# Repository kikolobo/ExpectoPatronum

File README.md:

# ExpectoPatronum_HW
Remote Lightning LED Fixture for performing lightshows. Based on NEO PIXELS, NRF24 Radios, Attiny84 MCU.

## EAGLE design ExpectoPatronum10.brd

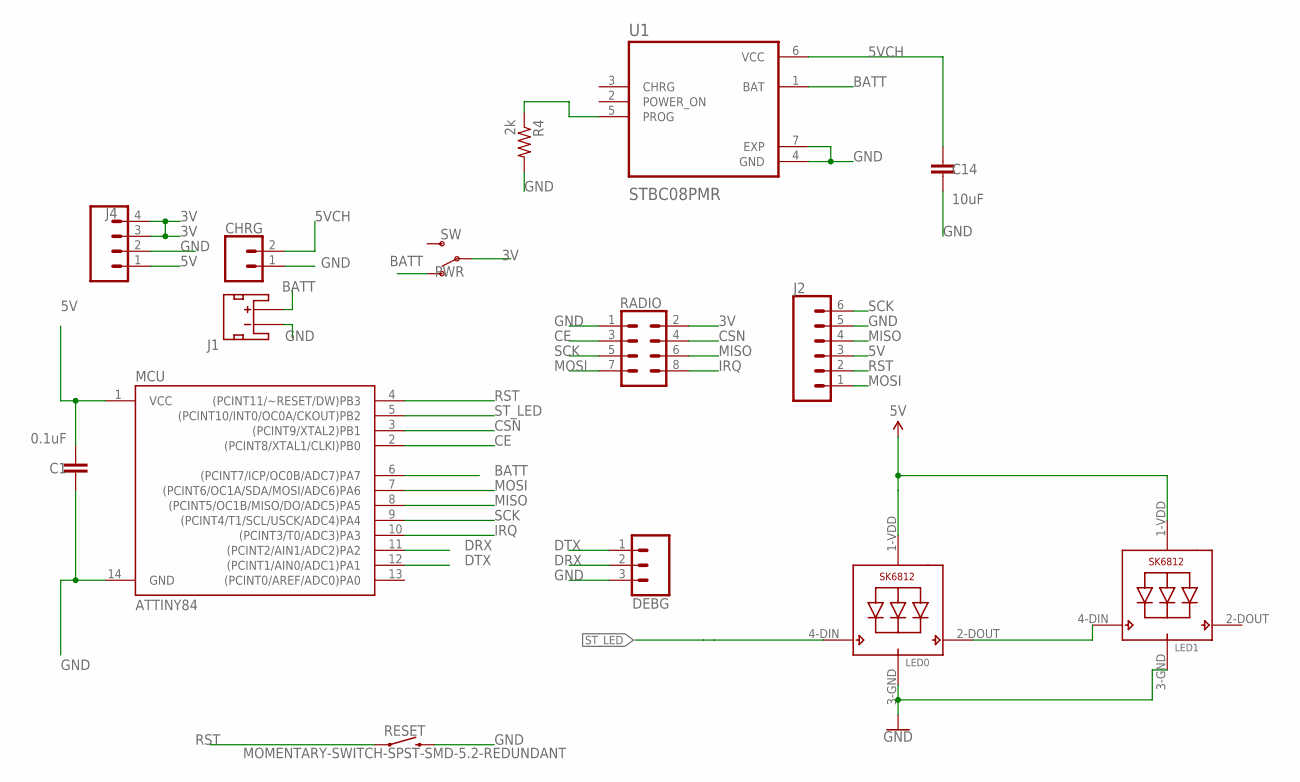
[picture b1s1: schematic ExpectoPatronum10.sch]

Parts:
C1: 0.1uF; 0603
C14: 10uF; 0603
CHRG: CONN_02; 1X02
DEBG: CONN_03; 1X03
J1: JST_2MM_MALE; JST-2-SMD
J2: CONN_06NO_SILK_FEMALE_PTH; 1X06_NO_SILK
J4: CONN_04; 1X04
LED0, LED1: SK6812_5050W; LED5050_W
MCU: ATTINY84; SO14
PWR: SW; SWITCH_SPST_SMD_A
R4: 2k; R0603
RADIO: CONN_04X2; 2X4
RESET: MOMENTARY-SWITCH-SPST-SMD-5.2-REDUNDANT; TACTILE_SWITCH_SMD_5.2MM
U1: STBC08PMR; SON95P300X300X100-7N

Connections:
3V: J4.3, J4.4, PWR.2, RADIO.2
5V: C1.2, J2.3, J4.1, LED0.1-VDD (VDD), LED1.1-VDD (VDD), MCU.1 (VCC)
5VCH: C14.1, CHRG.2, U1.6 (VCC)
BATT: J1.2 (+), MCU.6 ((PCINT7/ICP/OC0B/ADC7)PA7), PWR.1 (O), U1.1 (BAT)
CE: MCU.2 ((PCINT8/XTAL1/CLKI)PB0), RADIO.3
CSN: MCU.3 ((PCINT9/XTAL2)PB1), RADIO.4
DRX: DEBG.2, MCU.11 ((PCINT2/AIN1/ADC2)PA2)
DTX: DEBG.1, MCU.12 ((PCINT1/AIN0/ADC1)PA1)
GND: C1.1, C14.2, CHRG.1, DEBG.3, J1.1 (-), J2.5, J4.2, LED0.3-GND (GND), LED1.3-GND (GND), MCU.14 (GND), R4.2, RADIO.1, RESET.3 (2), RESET.4 (2), U1.4 (GND), U1.7 (EXP)
IRQ: MCU.10 ((PCINT3/T0/ADC3)PA3), RADIO.8
MISO: J2.4, MCU.8 ((PCINT5/OC1B/MISO/DO/ADC5)PA5), RADIO.6
MOSI: J2.1, MCU.7 ((PCINT6/OC1A/SDA/MOSI/ADC6)PA6), RADIO.7
unnamed: R4.1, U1.5 (PROG)
unnamed: LED0.2-DOUT (DO), LED1.4-DIN (DI)
RST: J2.2, MCU.4 ((PCINT11/~RESET/DW)PB3), RESET.1, RESET.2 (1)
SCK: J2.6, MCU.9 ((PCINT4/T1/SCL/USCK/ADC4)PA4), RADIO.5
ST_LED: LED0.4-DIN (DI), MCU.5 ((PCINT10/INT0/OC0A/CKOUT)PB2)

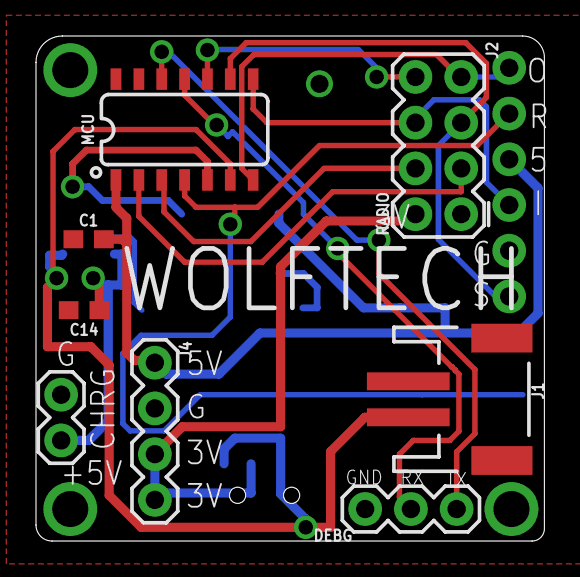
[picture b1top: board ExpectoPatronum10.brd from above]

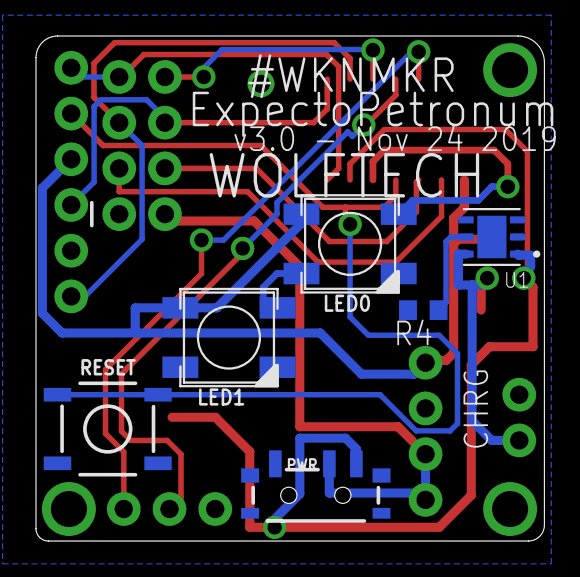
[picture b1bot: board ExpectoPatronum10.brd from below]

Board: 2 copper layers, 28.2 x 28.1 mm, 15 parts (6 on the bottom side), 17 nets.

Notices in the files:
parts and their libraries:
SparkFun-Connectors: Licensing: Creative Commons ShareAlike 4.0 International - https://creativecommons.org/licenses/by-sa/4.0
